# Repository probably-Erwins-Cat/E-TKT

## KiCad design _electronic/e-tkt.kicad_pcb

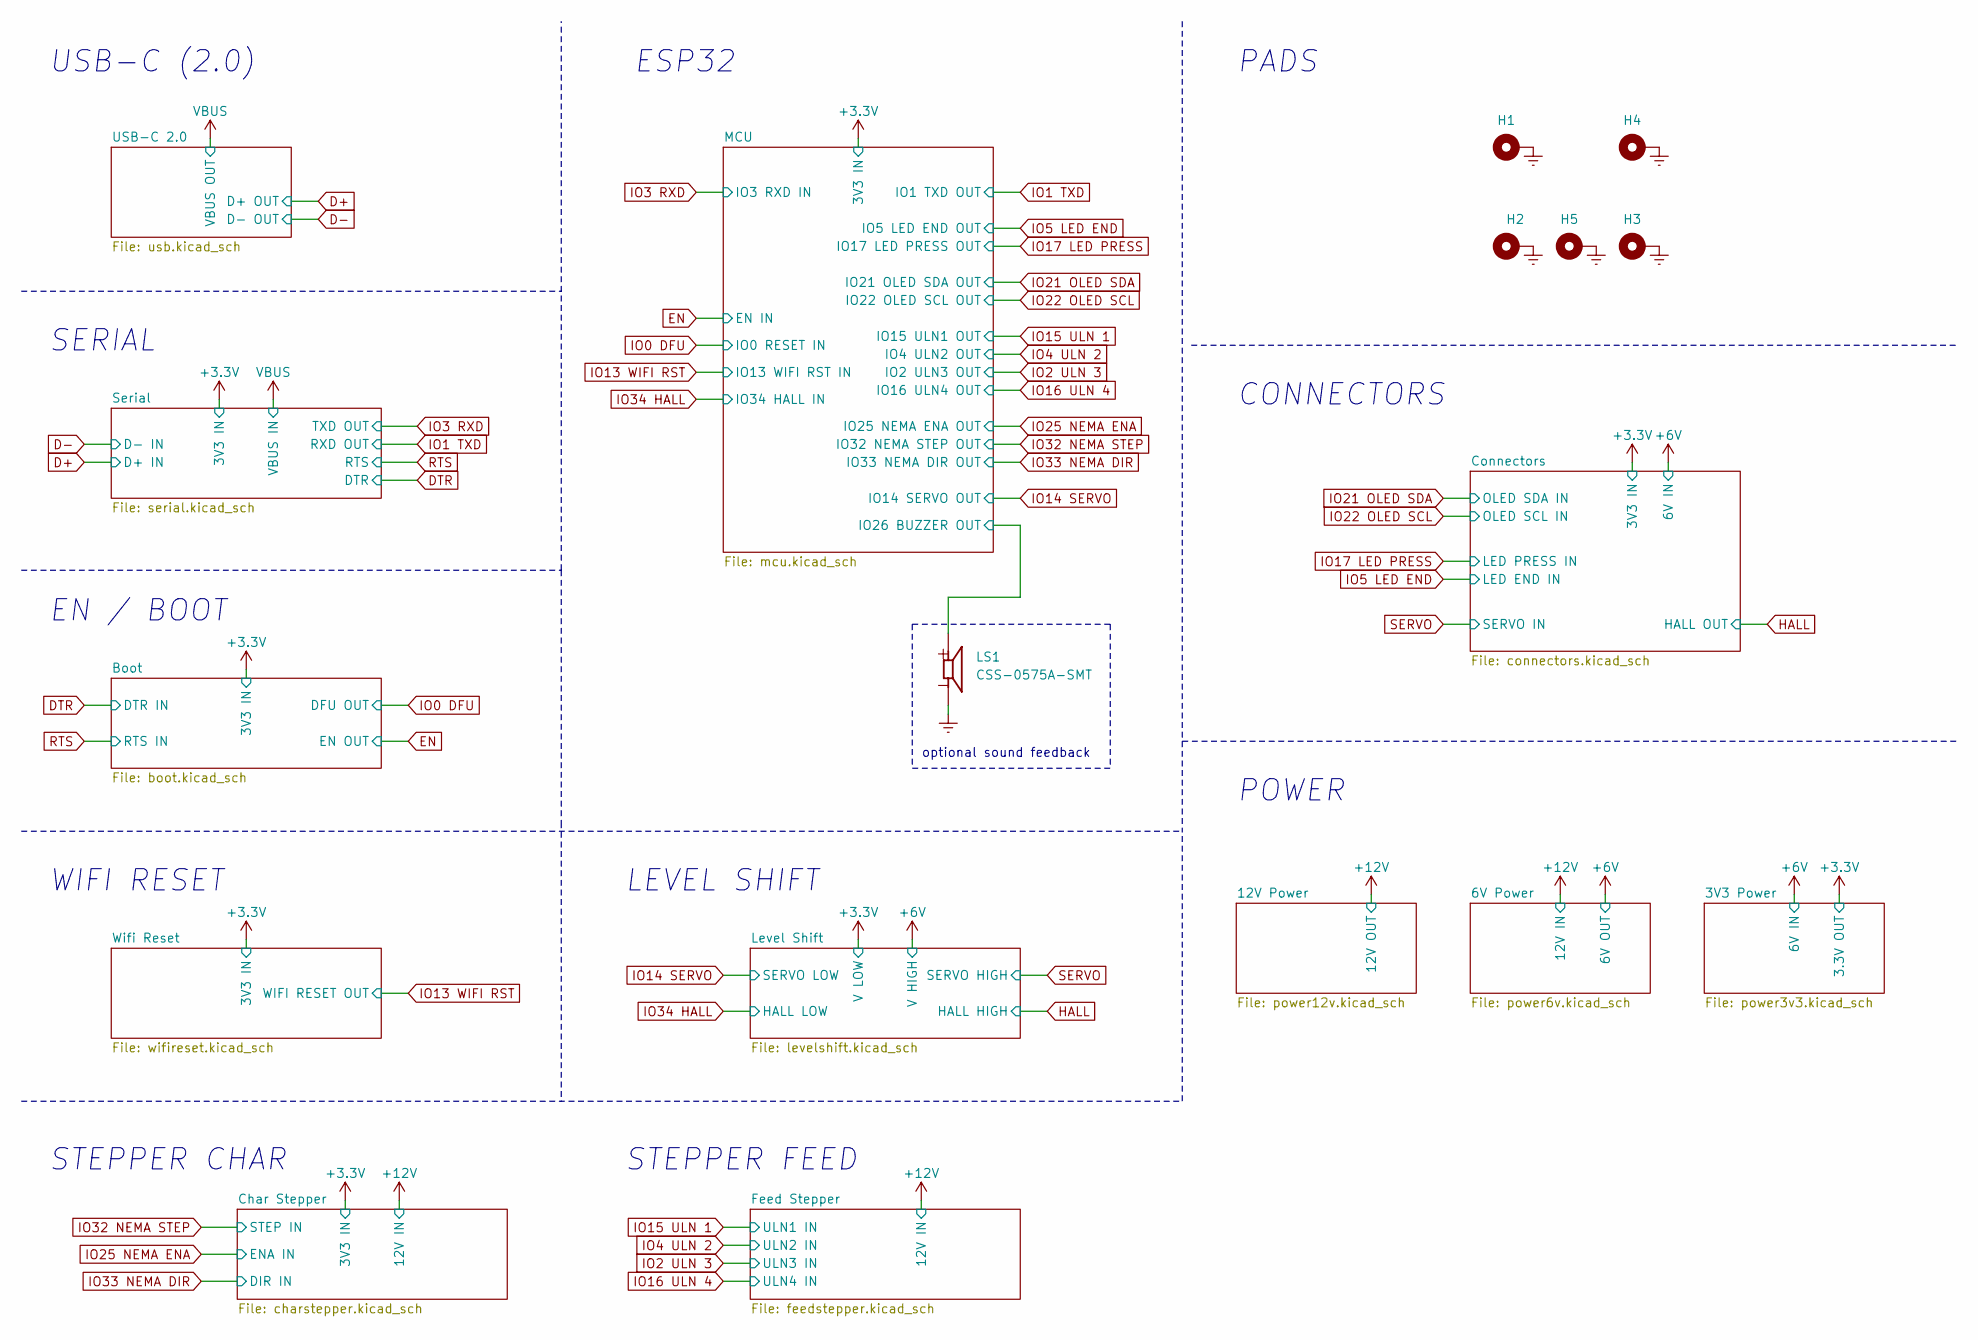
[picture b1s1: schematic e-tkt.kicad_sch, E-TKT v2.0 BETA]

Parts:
H1, H2, H3, H4, H5: M3; MountingHole_3.2mm_M3_Pad_Via; Mouser OK
LS1: CSS-0575A-SMT; BUZ-SMD_L5.0-W5.5-P4.60; Mouser OK

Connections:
/MCU/IO26 BUZZER OUT: LS1.1; also elsewhere on the board
GNDREF: H1.1, H2.1, H3.1, H4.1, H5.1, LS1.2; also elsewhere on the board

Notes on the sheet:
PADS
POWER
optional sound feedback
SERIAL
EN / BOOT
CONNECTORS
STEPPER CHAR
WIFI RESET
ESP32
LEVEL SHIFT
STEPPER FEED
USB-C (2.0)

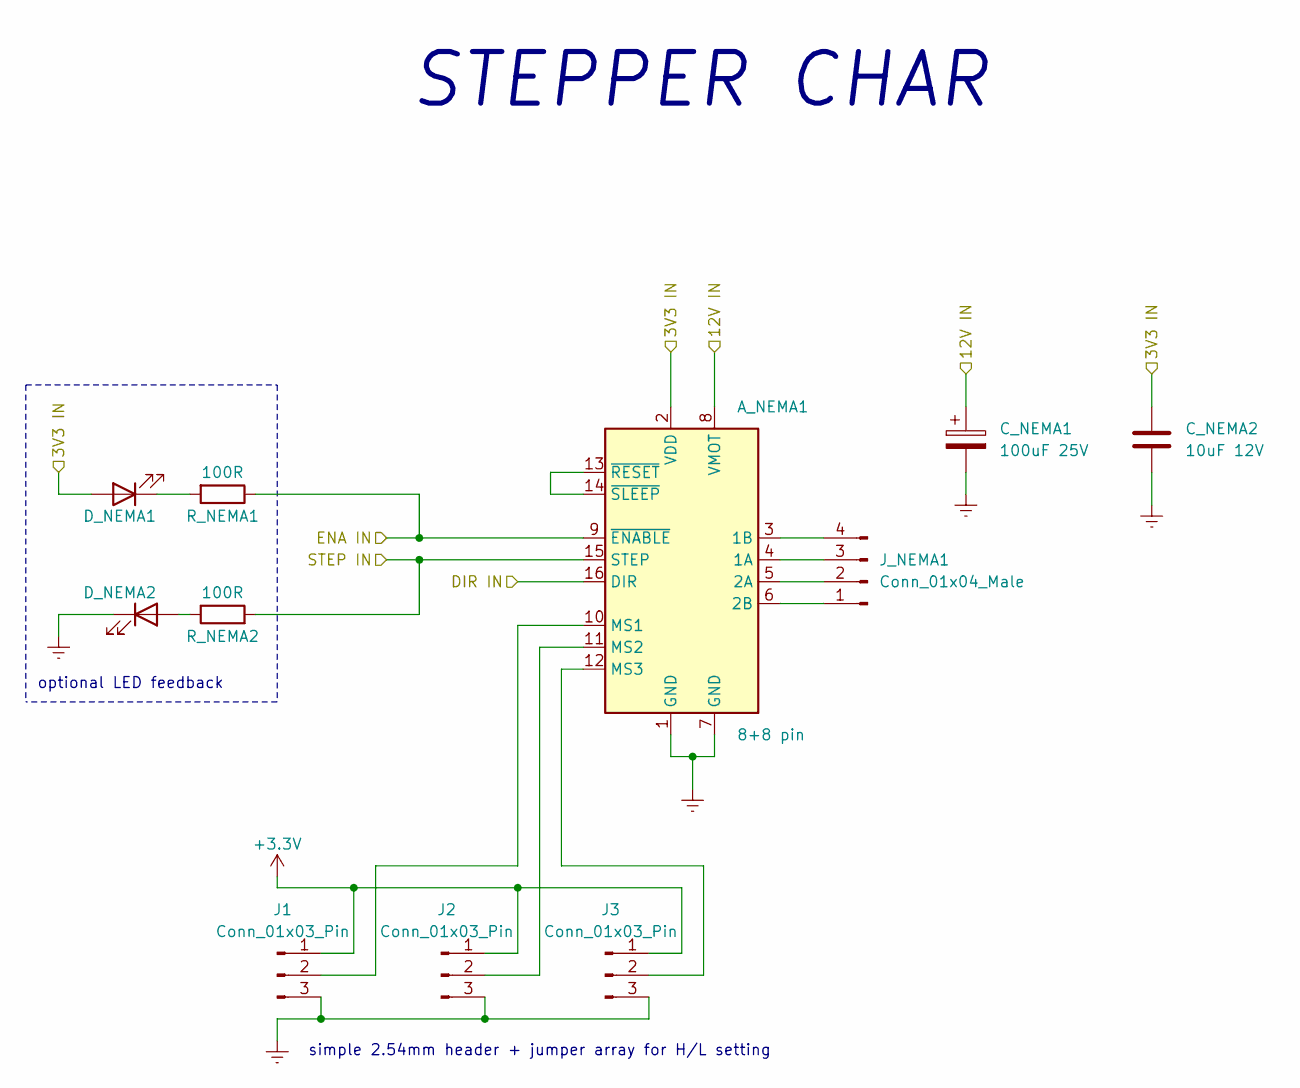
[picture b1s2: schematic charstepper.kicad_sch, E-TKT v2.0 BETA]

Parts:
A_NEMA1: 8+8 pin; Pololu_Breakout-16_15.2x20.3mm; Mouser OK
C_NEMA1: 100uF 25V; CP_Elec_6.3x7.7; Mouser OK
C_NEMA2: 10uF 12V; C_0603_1608Metric_Pad1.08x0.95mm_HandSolder; Mouser OK
D_NEMA1, D_NEMA2: LED white; LED_0603_1608Metric_Pad1.05x0.95mm_HandSolder; Mouser OK
J1, J2, J3: Conn_01x03_Pin; PinHeader_1x03_P2.54mm_Vertical; LCSC C2937625
J_NEMA1: Conn_01x04_Male; PinHeader_1x04_P2.54mm_Vertical; Mouser OK
R_NEMA1, R_NEMA2: 100R; R_0603_1608Metric_Pad0.98x0.95mm_HandSolder; Mouser OK

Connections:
+3.3V: A_NEMA1.2 (VDD), C_NEMA2.2, D_NEMA1.2 (A), J1.1, J2.1, J3.1; also elsewhere on the board
+12V: A_NEMA1.8 (VMOT), C_NEMA1.1; also elsewhere on the board
GNDREF: A_NEMA1.1 (GND), A_NEMA1.7 (GND), C_NEMA1.2, C_NEMA2.1, D_NEMA2.1 (K), J1.3, J2.3, J3.3; also elsewhere on the board
IO25 NEMA ENA: A_NEMA1.9 (~ENABLE), R_NEMA1.1; also elsewhere on the board
IO32 NEMA STEP: A_NEMA1.15 (STEP), R_NEMA2.2; also elsewhere on the board
IO33 NEMA DIR: A_NEMA1.16 (DIR); also elsewhere on the board
unnamed: A_NEMA1.4 (1A), J_NEMA1.3
unnamed: A_NEMA1.3 (1B), J_NEMA1.4
unnamed: A_NEMA1.5 (2A), J_NEMA1.2
unnamed: A_NEMA1.6 (2B), J_NEMA1.1
unnamed: A_NEMA1.10 (MS1), J1.2
unnamed: A_NEMA1.11 (MS2), J2.2
unnamed: A_NEMA1.12 (MS3), J3.2
unnamed: A_NEMA1.13 (~RESET), A_NEMA1.14 (~SLEEP)
unnamed: D_NEMA1.1 (K), R_NEMA1.2
unnamed: D_NEMA2.2 (A), R_NEMA2.1

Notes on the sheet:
optional LED feedback
simple 2.54mm header + jumper array for H/L setting
STEPPER CHAR

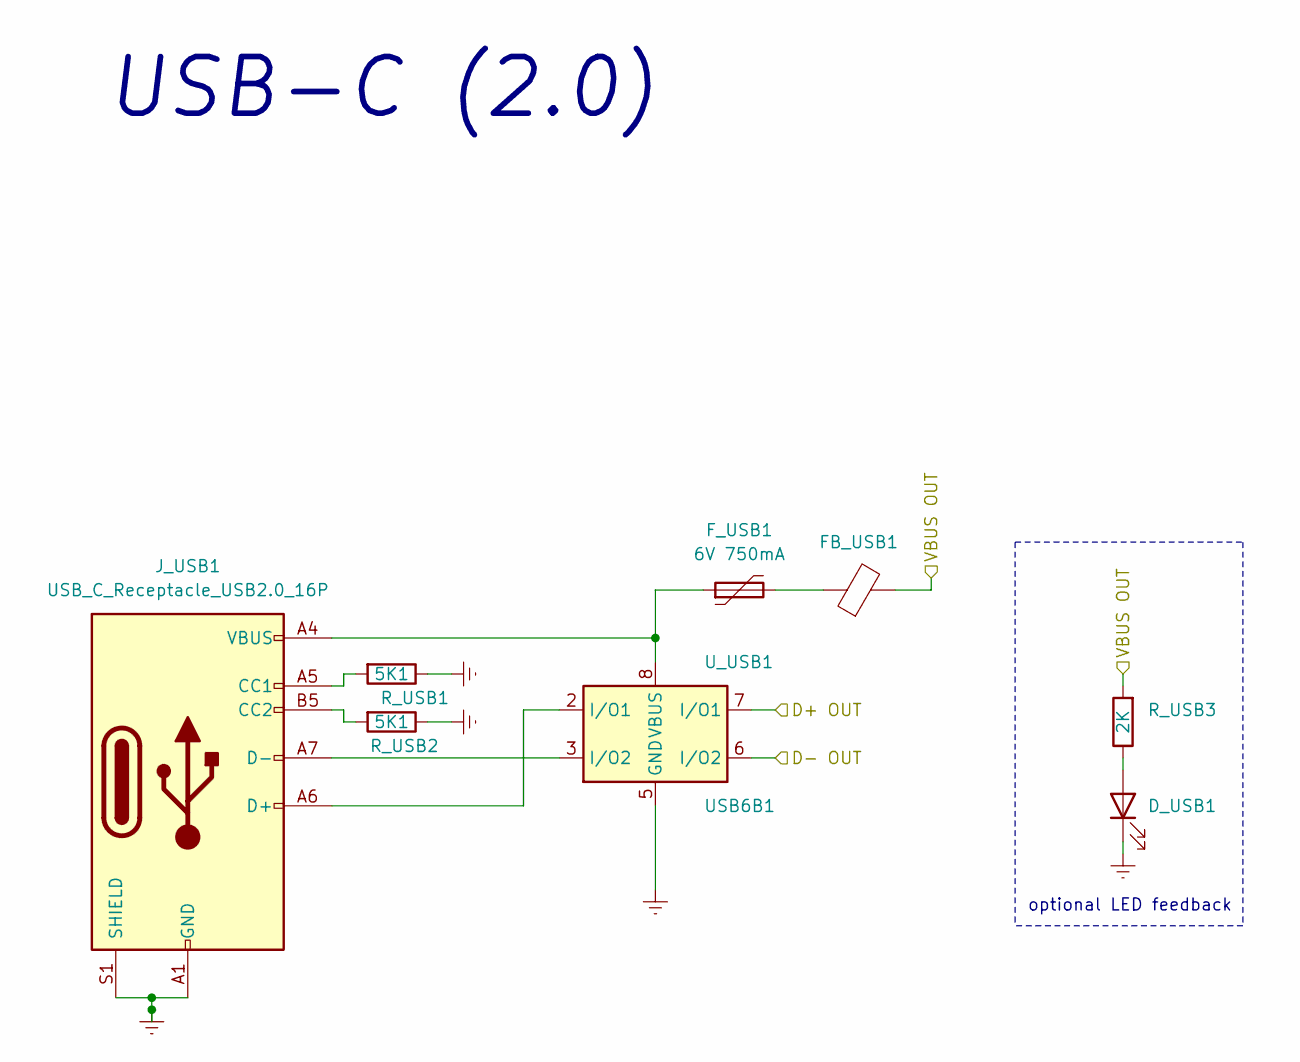
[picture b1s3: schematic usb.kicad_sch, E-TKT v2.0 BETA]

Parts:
D_USB1: LED white; LED_0603_1608Metric_Pad1.05x0.95mm_HandSolder; Mouser OK
FB_USB1: 40 Ohms @ 100 MHz 1 Power; L_0805_2012Metric_Pad1.05x1.20mm_HandSolder; Mouser OK
F_USB1: 6V 750mA; Fuse_0805_2012Metric_Pad1.15x1.40mm_HandSolder; Mouser OK
J_USB1: USB_C_Receptacle_USB2.0_16P; USB-TH_GT-USB-7057A; LCSC C22383830
R_USB1, R_USB2: 5K1; R_0603_1608Metric_Pad0.98x0.95mm_HandSolder; Mouser OK
R_USB3: 2K; R_0603_1608Metric_Pad0.98x0.95mm_HandSolder; Mouser OK
U_USB1: USB6B1; SOIC-8_3.9x4.9mm_P1.27mm; Mouser OK

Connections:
D+: U_USB1.7 (I/O1); also elsewhere on the board
D-: U_USB1.6 (I/O2); also elsewhere on the board
GNDREF: D_USB1.1 (K), J_USB1.A1 (GND), J_USB1.S1 (SHIELD), R_USB1.1, R_USB2.1, U_USB1.4 (GND), U_USB1.5 (GND); also elsewhere on the board
unnamed: D_USB1.2 (A), R_USB3.1
unnamed: FB_USB1.1, F_USB1.2
unnamed: F_USB1.1, J_USB1.A4 (VBUS), U_USB1.1 (VBUS), U_USB1.8 (VBUS)
unnamed: J_USB1.A5 (CC1), R_USB1.2
unnamed: J_USB1.B5 (CC2), R_USB2.2
unnamed: J_USB1.A6 (D+), U_USB1.2 (I/O1)
unnamed: J_USB1.A7 (D-), U_USB1.3 (I/O2)
VBUS: FB_USB1.2, R_USB3.2; also elsewhere on the board

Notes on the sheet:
USB-C (2.0)
optional LED feedback

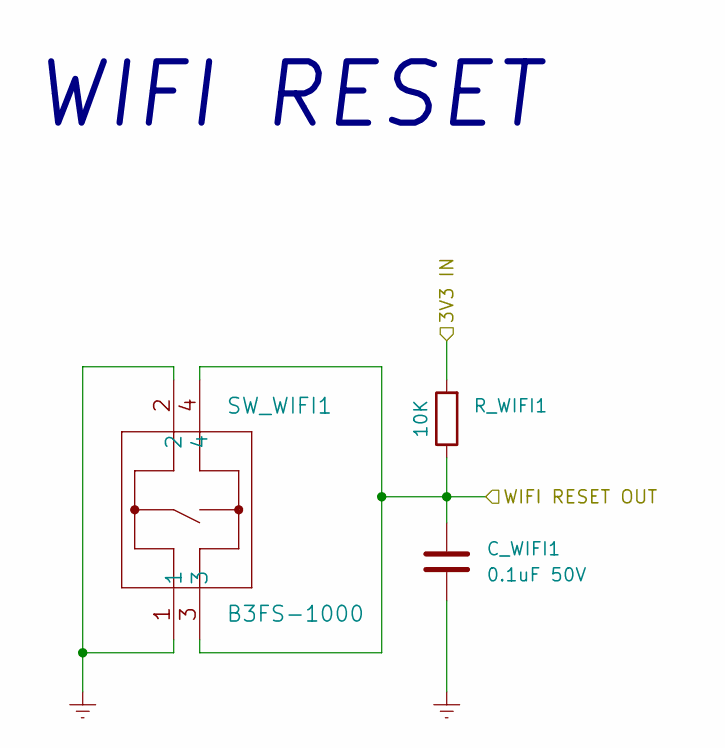
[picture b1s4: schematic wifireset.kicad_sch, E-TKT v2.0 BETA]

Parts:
C_WIFI1: 0.1uF 50V; C_0603_1608Metric_Pad1.08x0.95mm_HandSolder; Mouser OK
R_WIFI1: 10K; R_0603_1608Metric_Pad0.98x0.95mm_HandSolder; Mouser OK
SW_WIFI1: B3FS-1000; KEY-SMD_4P-L6.0-W6.3-P4.50-LS8.0; Mouser OK

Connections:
+3.3V: R_WIFI1.2; also elsewhere on the board
GNDREF: C_WIFI1.1, SW_WIFI1.1, SW_WIFI1.2; also elsewhere on the board
IO13 WIFI RST: C_WIFI1.2, R_WIFI1.1, SW_WIFI1.3, SW_WIFI1.4; also elsewhere on the board

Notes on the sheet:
WIFI RESET

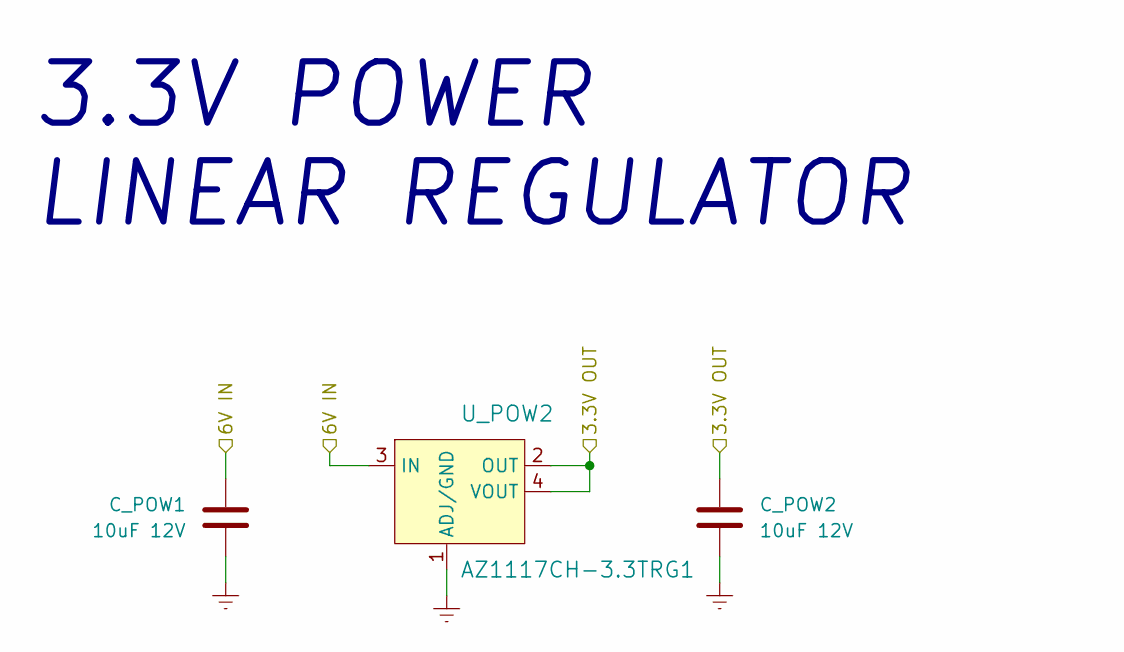
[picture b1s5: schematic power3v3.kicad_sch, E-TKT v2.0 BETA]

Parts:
C_POW1, C_POW2: 10uF 12V; C_0603_1608Metric_Pad1.08x0.95mm_HandSolder; Mouser OK
U_POW2: AZ1117CH-3.3TRG1; SOT-223; Mouser OK

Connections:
+3.3V: C_POW2.1, U_POW2.2 (OUT), U_POW2.4 (VOUT); also elsewhere on the board
+6V: C_POW1.1, U_POW2.3 (IN); also elsewhere on the board
GNDREF: C_POW1.2, C_POW2.2, U_POW2.1 (ADJ/GND); also elsewhere on the board

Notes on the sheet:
3.3V POWER LINEAR REGULATOR

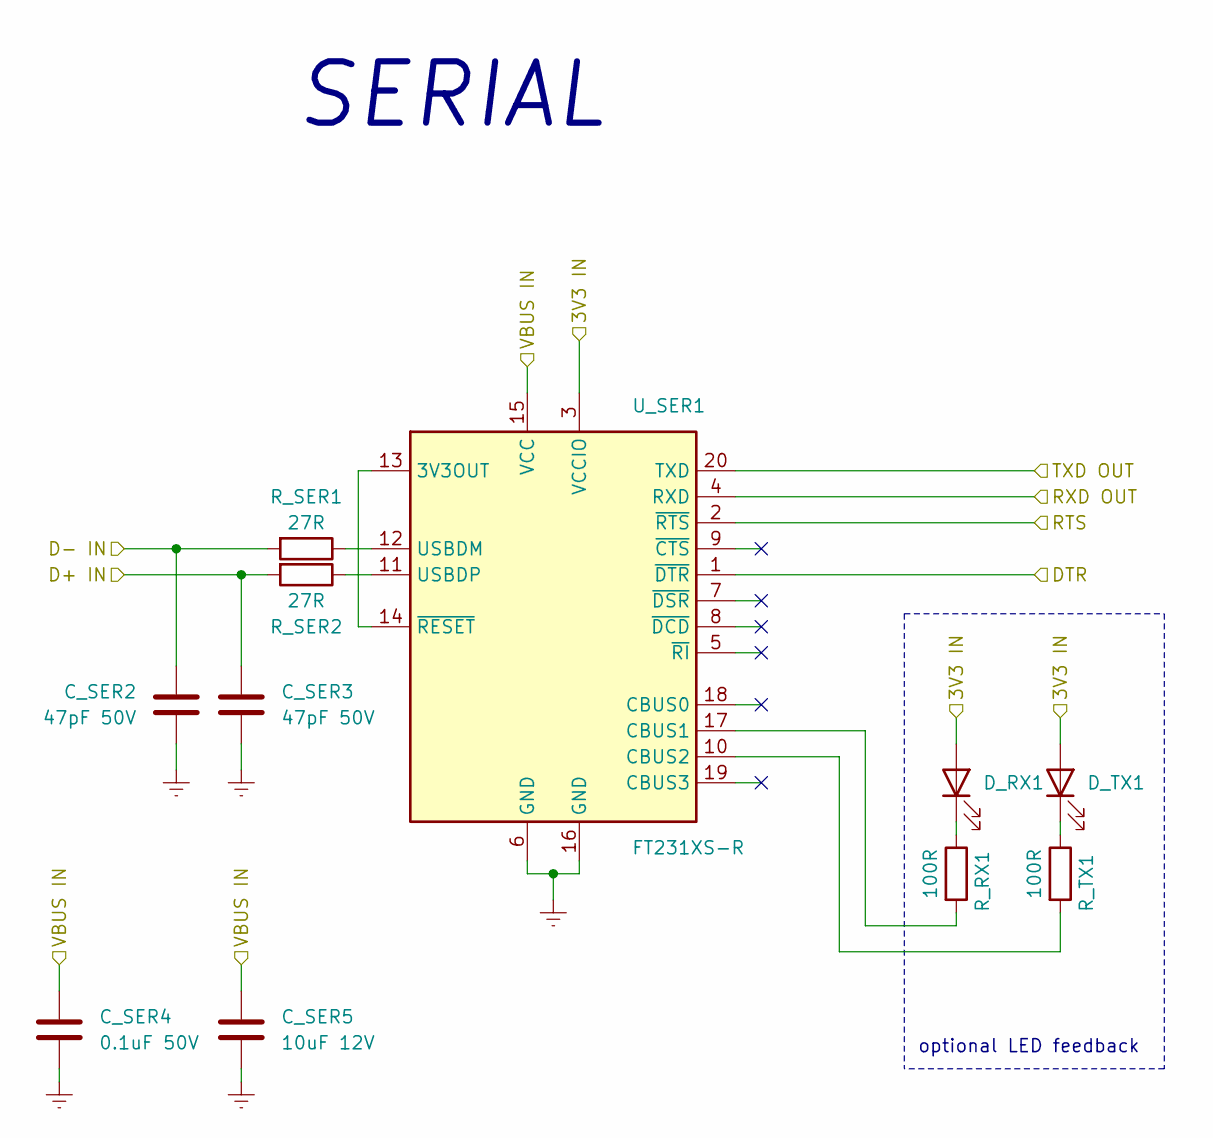
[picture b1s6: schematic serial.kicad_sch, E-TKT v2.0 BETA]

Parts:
C_SER2, C_SER3: 47pF 50V; C_0603_1608Metric_Pad1.08x0.95mm_HandSolder; Mouser OK
C_SER4: 0.1uF 50V; C_0603_1608Metric_Pad1.08x0.95mm_HandSolder; Mouser OK
C_SER5: 10uF 12V; C_0603_1608Metric_Pad1.08x0.95mm_HandSolder; Mouser OK
D_RX1: LED white; LED_0603_1608Metric_Pad1.05x0.95mm_HandSolder; Mouser OK
D_TX1: LED white; LED_0603_1608Metric_Pad1.05x0.95mm_HandSolder; Mouser OK
R_RX1: 100R; R_0603_1608Metric_Pad0.98x0.95mm_HandSolder; Mouser OK
R_SER1, R_SER2: 27R; R_0603_1608Metric_Pad0.98x0.95mm_HandSolder; Mouser OK
R_TX1: 100R; R_0603_1608Metric_Pad0.98x0.95mm_HandSolder; Mouser OK
U_SER1: FT231XS-R; SSOP-20_3.9x8.7mm_P0.635mm; Mouser OK

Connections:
+3.3V: D_RX1.2 (A), D_TX1.2 (A), U_SER1.3 (VCCIO); also elsewhere on the board
D+: C_SER3.2, R_SER2.2; also elsewhere on the board
D-: C_SER2.2, R_SER1.2; also elsewhere on the board
DTR: U_SER1.1 (~DTR); also elsewhere on the board
GNDREF: C_SER2.1, C_SER3.1, C_SER4.2, C_SER5.1, U_SER1.6 (GND), U_SER1.16 (GND); also elsewhere on the board
IO1 TXD: U_SER1.4 (RXD); also elsewhere on the board
IO3 RXD: U_SER1.20 (TXD); also elsewhere on the board
unnamed: D_RX1.1 (K), R_RX1.1
unnamed: D_TX1.1 (K), R_TX1.1
unnamed: U_SER1.13 (3V3OUT), U_SER1.14 (~RESET)
unnamed: R_RX1.2, U_SER1.17 (CBUS1)
unnamed: R_TX1.2, U_SER1.10 (CBUS2)
unnamed: R_SER1.1, U_SER1.12 (USBDM)
unnamed: R_SER2.1, U_SER1.11 (USBDP)
RTS: U_SER1.2 (~RTS); also elsewhere on the board
VBUS: C_SER4.1, C_SER5.2, U_SER1.15 (VCC); also elsewhere on the board

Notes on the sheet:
SERIAL
optional LED feedback

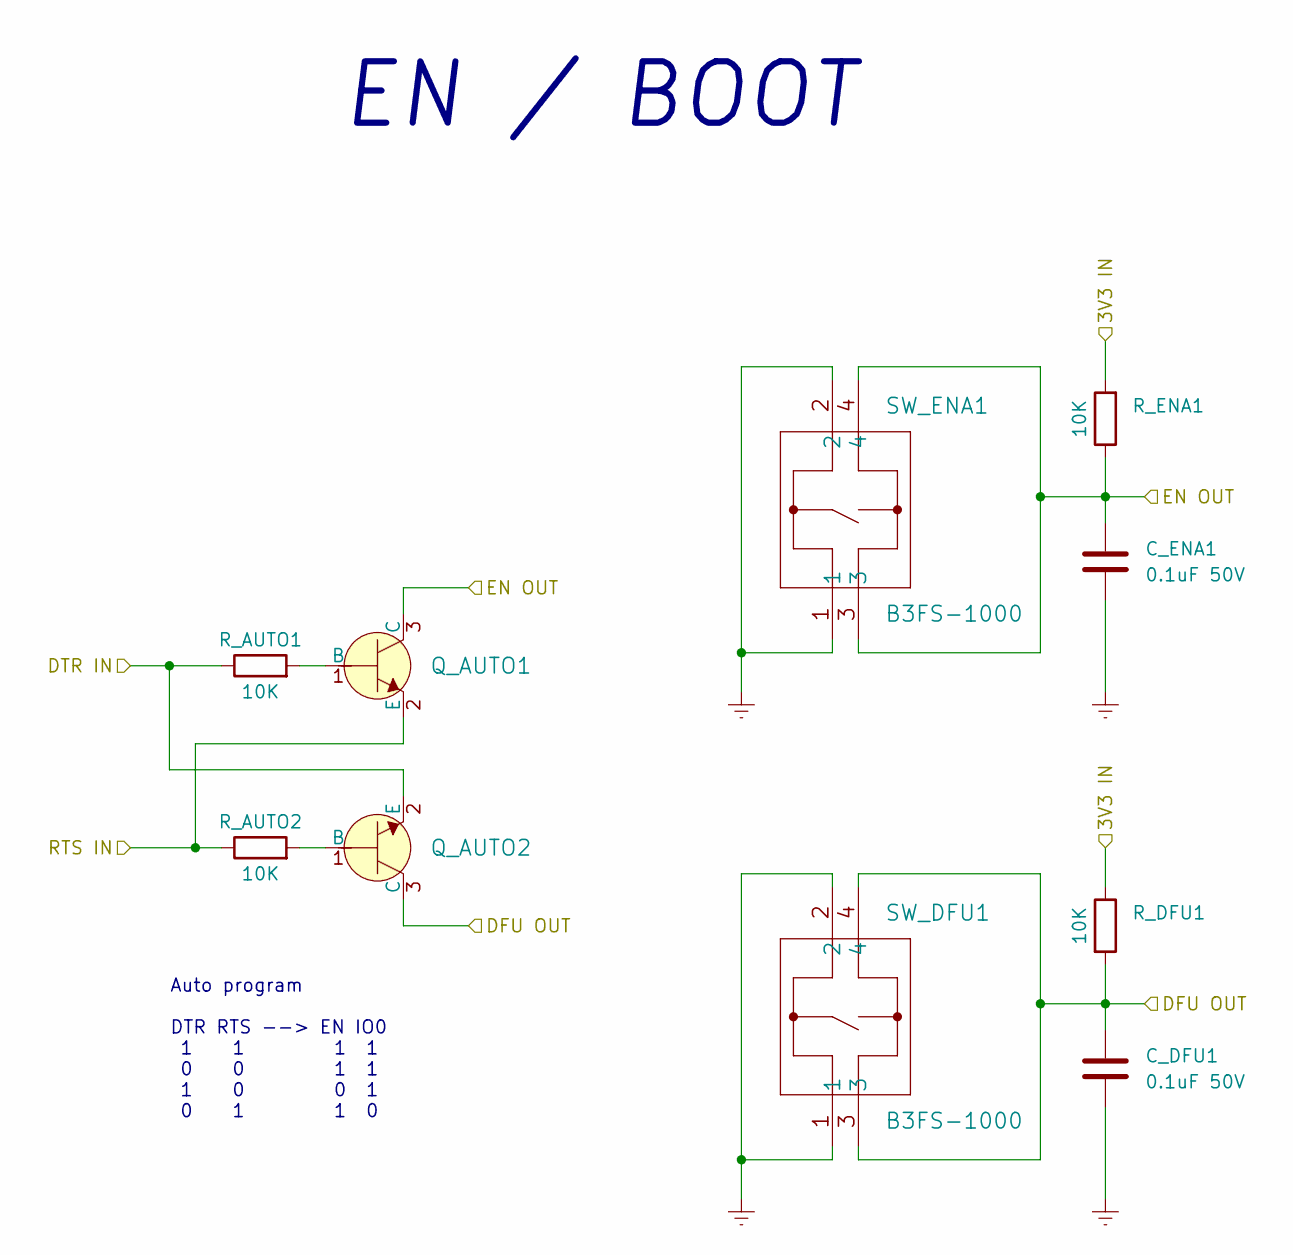
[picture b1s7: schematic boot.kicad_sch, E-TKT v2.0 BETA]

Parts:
C_DFU1: 0.1uF 50V; C_0603_1608Metric_Pad1.08x0.95mm_HandSolder; Mouser OK
C_ENA1: 0.1uF 50V; C_0603_1608Metric_Pad1.08x0.95mm_HandSolder; Mouser OK
Q_AUTO1, Q_AUTO2: SS8050; SOT-23_Handsoldering; Mouser OK
R_AUTO1, R_AUTO2: 10K; R_0603_1608Metric_Pad0.98x0.95mm_HandSolder; Mouser OK
R_DFU1: 10K; R_0603_1608Metric_Pad0.98x0.95mm_HandSolder; Mouser OK
R_ENA1: 10K; R_0603_1608Metric_Pad0.98x0.95mm_HandSolder; Mouser OK
SW_DFU1: B3FS-1000; KEY-SMD_4P-L6.0-W6.3-P4.50-LS8.0; Mouser OK
SW_ENA1: B3FS-1000; KEY-SMD_4P-L6.0-W6.3-P4.50-LS8.0; Mouser OK

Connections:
+3.3V: R_DFU1.1, R_ENA1.2; also elsewhere on the board
DTR: Q_AUTO2.2 (E), R_AUTO1.1; also elsewhere on the board
EN: C_ENA1.2, Q_AUTO1.3 (C), R_ENA1.1, SW_ENA1.3, SW_ENA1.4; also elsewhere on the board
GNDREF: C_DFU1.1, C_ENA1.1, SW_DFU1.1, SW_DFU1.2, SW_ENA1.1, SW_ENA1.2; also elsewhere on the board
IO0 DFU: C_DFU1.2, Q_AUTO2.3 (C), R_DFU1.2, SW_DFU1.3, SW_DFU1.4; also elsewhere on the board
unnamed: Q_AUTO1.1 (B), R_AUTO1.2
unnamed: Q_AUTO2.1 (B), R_AUTO2.2
RTS: Q_AUTO1.2 (E), R_AUTO2.1; also elsewhere on the board

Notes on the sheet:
Auto program DTR RTS --> EN IO0 1 1 1 1 0 0 1 1 1 0 0 1 0 1 1 0
EN / BOOT

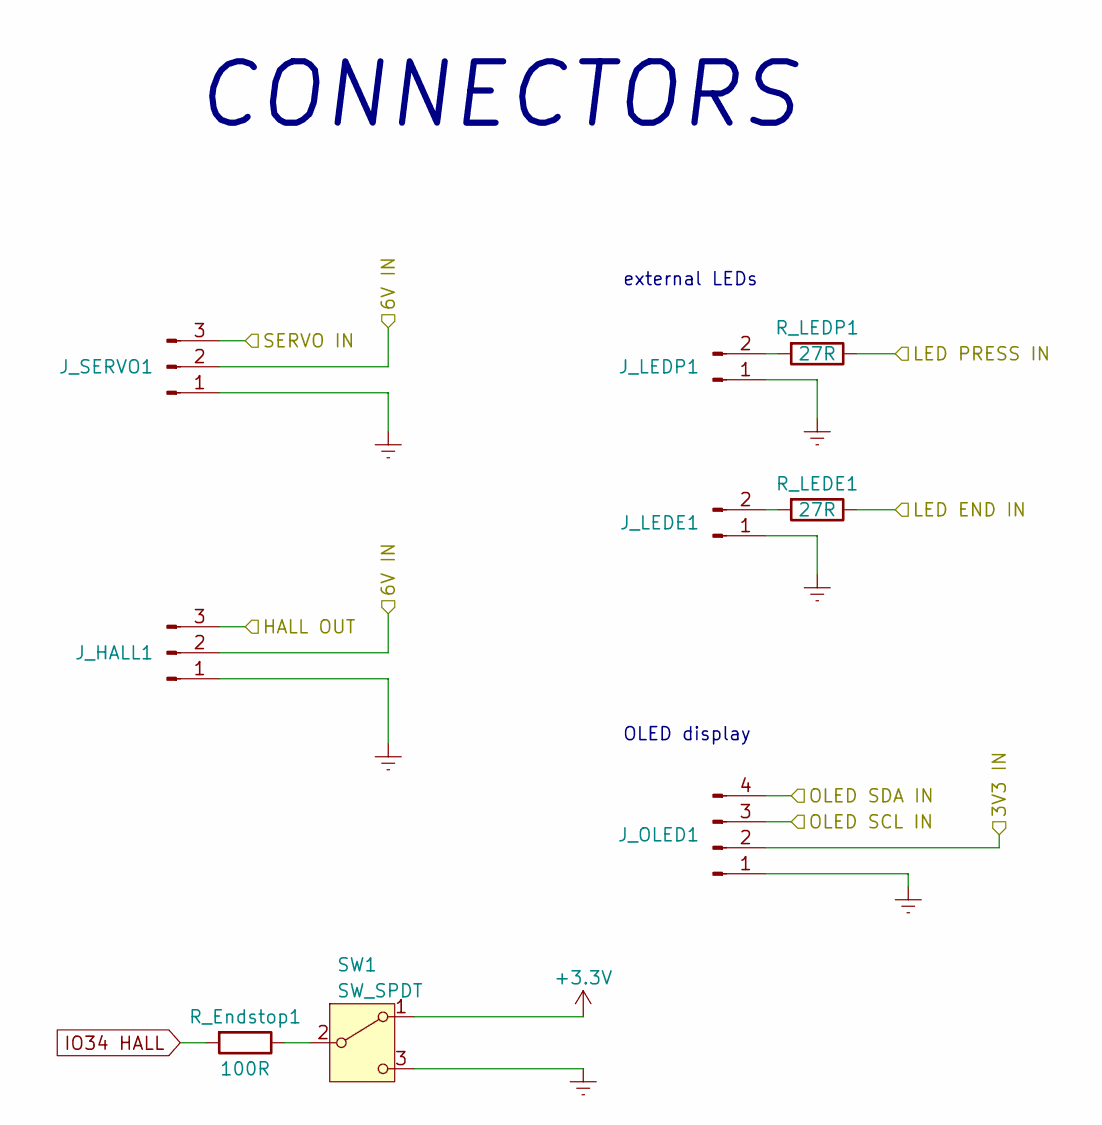
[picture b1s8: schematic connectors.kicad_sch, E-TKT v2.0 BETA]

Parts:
J_HALL1: Conn_01x03_Female; PinHeader_1x03_P2.54mm_Vertical; Mouser OK
J_LEDE1: Conn_01x02_Male; PinHeader_1x02_P2.54mm_Vertical; Mouser OK
J_LEDP1: Conn_01x02_Male; PinHeader_1x02_P2.54mm_Vertical; Mouser OK
J_OLED1: Conn_01x04_Male; PinHeader_1x04_P2.54mm_Vertical; Mouser OK
J_SERVO1: Conn_01x03_Male; PinHeader_1x03_P2.54mm_Vertical; Mouser OK
R_Endstop1: 100R; R_0603_1608Metric_Pad0.98x0.95mm_HandSolder; Mouser OK
R_LEDE1: 27R; R_0603_1608Metric_Pad0.98x0.95mm_HandSolder; Mouser OK
R_LEDP1: 27R; R_0603_1608Metric_Pad0.98x0.95mm_HandSolder; Mouser OK
SW1: SW_SPDT; SW-TH_JL010; LCSC C2681582

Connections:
+3.3V: J_OLED1.2, SW1.1 (A); also elsewhere on the board
+6V: J_HALL1.2, J_SERVO1.2; also elsewhere on the board
GNDREF: J_HALL1.1, J_LEDE1.1, J_LEDP1.1, J_OLED1.1, J_SERVO1.1, SW1.3 (C); also elsewhere on the board
HALL: J_HALL1.3; also elsewhere on the board
IO5 LED END: R_LEDE1.1; also elsewhere on the board
IO17 LED PRESS: R_LEDP1.1; also elsewhere on the board
IO21 OLED SDA: J_OLED1.4; also elsewhere on the board
IO22 OLED SCL: J_OLED1.3; also elsewhere on the board
IO34 HALL: R_Endstop1.2; also elsewhere on the board
unnamed: J_LEDE1.2, R_LEDE1.2
unnamed: J_LEDP1.2, R_LEDP1.2
unnamed: R_Endstop1.1, SW1.2 (B)
SERVO: J_SERVO1.3; also elsewhere on the board

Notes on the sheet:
OLED display
CONNECTORS
external LEDs

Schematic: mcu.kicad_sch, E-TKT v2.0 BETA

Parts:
C_MCU1: 0.1uF 50V; C_0603_1608Metric_Pad1.08x0.95mm_HandSolder; Mouser OK
C_MCU2: 10uF 12V; C_0603_1608Metric_Pad1.08x0.95mm_HandSolder; Mouser OK
U_MCU1: ESP32-WROOM-32; Mouser OK

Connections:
+3.3V: C_MCU1.1, C_MCU2.2, U_MCU1.2 (VDD); also elsewhere on the board
/MCU/IO26 BUZZER OUT: U_MCU1.11 (IO26); also elsewhere on the board
EN: U_MCU1.3 (EN); also elsewhere on the board
GNDREF: C_MCU1.2, C_MCU2.1, U_MCU1.1 (GND), U_MCU1.15 (GND), U_MCU1.38 (GND), U_MCU1.39 (GND); also elsewhere on the board
IO0 DFU: U_MCU1.25 (IO0); also elsewhere on the board
IO1 TXD: U_MCU1.35 (TXD0/IO1); also elsewhere on the board
IO2 ULN 3: U_MCU1.24 (IO2); also elsewhere on the board
IO3 RXD: U_MCU1.34 (RXD0/IO3); also elsewhere on the board
IO4 ULN 2: U_MCU1.26 (IO4); also elsewhere on the board
IO5 LED END: U_MCU1.29 (IO5); also elsewhere on the board
IO13 WIFI RST: U_MCU1.16 (IO13); also elsewhere on the board
IO14 SERVO: U_MCU1.13 (IO14); also elsewhere on the board
IO15 ULN 1: U_MCU1.23 (IO15); also elsewhere on the board
IO16 ULN 4: U_MCU1.27 (IO16); also elsewhere on the board
IO17 LED PRESS: U_MCU1.28 (IO17); also elsewhere on the board
IO21 OLED SDA: U_MCU1.33 (IO21); also elsewhere on the board
IO22 OLED SCL: U_MCU1.36 (IO22); also elsewhere on the board
IO25 NEMA ENA: U_MCU1.10 (IO25); also elsewhere on the board
IO32 NEMA STEP: U_MCU1.8 (IO32); also elsewhere on the board
IO33 NEMA DIR: U_MCU1.9 (IO33); also elsewhere on the board
IO34 HALL: U_MCU1.6 (IO34); also elsewhere on the board

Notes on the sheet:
ESP32

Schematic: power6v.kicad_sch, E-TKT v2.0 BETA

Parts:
C_POW_6V_FF1: 47pF 50V; C_0603_1608Metric_Pad1.08x0.95mm_HandSolder; Mouser OK
C_POW_BST1: 0.1uF 50V; C_0603_1608Metric_Pad1.08x0.95mm_HandSolder; Mouser OK
C_POW_IN1, C_POW_IN2, C_POW_IN3: 22uF 25V; C_1210_3225Metric_Pad1.33x2.70mm_HandSolder; Mouser OK
C_POW_OUT1, C_POW_OUT2, C_POW_OUT3, C_POW_OUT4, C_POW_OUT5: 22uF 25V; C_1210_3225Metric_Pad1.33x2.70mm_HandSolder; Mouser OK
L1: SRP6060FA-100M; IND-SMD_L8.5-W8.0_PSPMAA0803H-330M-ANP; Mouser OK
R_POW_FBT1: 100K; R_0603_1608Metric_Pad0.98x0.95mm_HandSolder; Mouser OK
R_POW_FFB1: 11K; R_0603_1608Metric_Pad0.98x0.95mm_HandSolder; Mouser OK
U_POW1: SOT-23-6_Handsoldering; Mouser N

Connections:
+6V: C_POW_6V_FF1.1, C_POW_OUT1.1, C_POW_OUT2.1, C_POW_OUT3.1, C_POW_OUT4.1, C_POW_OUT5.1, L1.2, R_POW_FBT1.2; also elsewhere on the board
+12V: C_POW_IN1.1, C_POW_IN2.1, C_POW_IN3.1, U_POW1.3 (VIN); also elsewhere on the board
GNDREF: C_POW_IN1.2, C_POW_IN2.2, C_POW_IN3.2, C_POW_OUT1.2, C_POW_OUT2.2, C_POW_OUT3.2, C_POW_OUT4.2, C_POW_OUT5.2, R_POW_FFB1.1, U_POW1.1 (GND); also elsewhere on the board
unnamed: C_POW_BST1.1, U_POW1.6 (BOOT)
unnamed: C_POW_6V_FF1.2, R_POW_FBT1.1, R_POW_FFB1.2, U_POW1.4 (FB)
unnamed: C_POW_BST1.2, L1.1, U_POW1.2 (SW)

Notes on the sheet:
6V POWER BUCK CONVERTER

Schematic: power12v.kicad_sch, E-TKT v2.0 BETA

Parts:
D_POW2: LED white; LED_0603_1608Metric_Pad1.05x0.95mm_HandSolder; Mouser OK
J_POW1: Barrel_Jack_Switch; BarrelJack_Horizontal; Mouser OK
J_USB2: USB_C_Receptacle_USB2.0_14P; USB-TH_GT-USB-7057A; LCSC C22383830
R_POW6: 5K1; R_0603_1608Metric_Pad0.98x0.95mm_HandSolder; Mouser OK
U1: HUSB237-AA001-DN06R; TDFN-6_L2.0-W2.0-P0.65-TL-EP; LCSC Part C22373734

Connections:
+12V: J_POW1.1, J_USB2.A4 (VBUS), R_POW6.1, U1.2 (VUSB); also elsewhere on the board
GNDREF: D_POW2.1 (K), J_POW1.2, J_POW1.3, J_USB2.A1 (GND), J_USB2.S1 (SHIELD), U1.7 (GND); also elsewhere on the board
unnamed: D_POW2.2 (A), R_POW6.2
unnamed: J_USB2.A5 (CC1), U1.1 (CC1)
unnamed: J_USB2.B5 (CC2), U1.6 (CC2)

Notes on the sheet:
Vset = floating =12V
optional LED feedback
12V POWER + LATCH SWITCH

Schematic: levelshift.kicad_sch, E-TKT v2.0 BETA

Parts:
D_HALL1: LED white; LED_0603_1608Metric_Pad1.05x0.95mm_HandSolder; Mouser OK
D_SERVO1: LED white; LED_0603_1608Metric_Pad1.05x0.95mm_HandSolder; Mouser OK
Q_HALL1: BSS138LT3G; SOT-23_Handsoldering; Mouser OK
Q_SERVO1: BSS138LT3G; SOT-23_Handsoldering; Mouser OK
R_HALL1, R_HALL2: 10K; R_0603_1608Metric_Pad0.98x0.95mm_HandSolder; Mouser OK
R_HALL3: 100R; R_0603_1608Metric_Pad0.98x0.95mm_HandSolder; Mouser OK
R_SERVO1, R_SERVO2: 10K; R_0603_1608Metric_Pad0.98x0.95mm_HandSolder; Mouser OK
R_SERVO3: 100R; R_0603_1608Metric_Pad0.98x0.95mm_HandSolder; Mouser OK

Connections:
+3.3V: D_HALL1.2 (A), D_SERVO1.2 (A), Q_HALL1.1 (G), Q_SERVO1.1 (G), R_HALL2.2, R_SERVO2.2; also elsewhere on the board
+6V: R_HALL1.2, R_SERVO1.2; also elsewhere on the board
HALL: Q_HALL1.3 (D), R_HALL1.1; also elsewhere on the board
IO14 SERVO: Q_SERVO1.2 (S), R_SERVO2.1, R_SERVO3.1; also elsewhere on the board
IO34 HALL: Q_HALL1.2 (S), R_HALL2.1, R_HALL3.1; also elsewhere on the board
unnamed: D_HALL1.1 (K), R_HALL3.2
unnamed: D_SERVO1.1 (K), R_SERVO3.2
SERVO: Q_SERVO1.3 (D), R_SERVO1.1; also elsewhere on the board

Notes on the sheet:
optional LED feedback
LEVEL SHIFT

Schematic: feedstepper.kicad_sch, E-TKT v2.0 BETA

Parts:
C_STP1: 10uF 12V; C_0603_1608Metric_Pad1.08x0.95mm_HandSolder; Mouser OK
D_STP1, D_STP2, D_STP3, D_STP4: LED white; LED_0603_1608Metric_Pad1.05x0.95mm_HandSolder; Mouser OK
J_28byj-48-12v_1: Conn_01x05_Male; PinHeader_1x05_P2.54mm_Vertical; Mouser OK
R_STP1, R_STP2, R_STP3, R_STP4: 5K1; R_0603_1608Metric_Pad0.98x0.95mm_HandSolder; Mouser OK
U_STP1: ULN2003; SOIC-16_3.9x9.9mm_P1.27mm; Mouser OK

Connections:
+12V: C_STP1.2, J_28byj-48-12v_1.1, R_STP1.1, R_STP2.1, R_STP3.1, R_STP4.1, U_STP1.9 (COM); also elsewhere on the board
GNDREF: C_STP1.1, U_STP1.8 (GND); also elsewhere on the board
IO2 ULN 3: U_STP1.3 (I3); also elsewhere on the board
IO4 ULN 2: U_STP1.2 (I2); also elsewhere on the board
IO15 ULN 1: U_STP1.1 (I1); also elsewhere on the board
IO16 ULN 4: U_STP1.4 (I4); also elsewhere on the board
unnamed: D_STP1.2 (A), R_STP1.2
unnamed: D_STP1.1 (K), J_28byj-48-12v_1.2, U_STP1.16 (O1)
unnamed: D_STP2.2 (A), R_STP2.2
unnamed: D_STP2.1 (K), J_28byj-48-12v_1.3, U_STP1.15 (O2)
unnamed: D_STP3.2 (A), R_STP3.2
unnamed: D_STP3.1 (K), J_28byj-48-12v_1.4, U_STP1.14 (O3)
unnamed: D_STP4.2 (A), R_STP4.2
unnamed: D_STP4.1 (K), J_28byj-48-12v_1.5, U_STP1.13 (O4)

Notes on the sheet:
optional LED feedback
STEPPER FEED

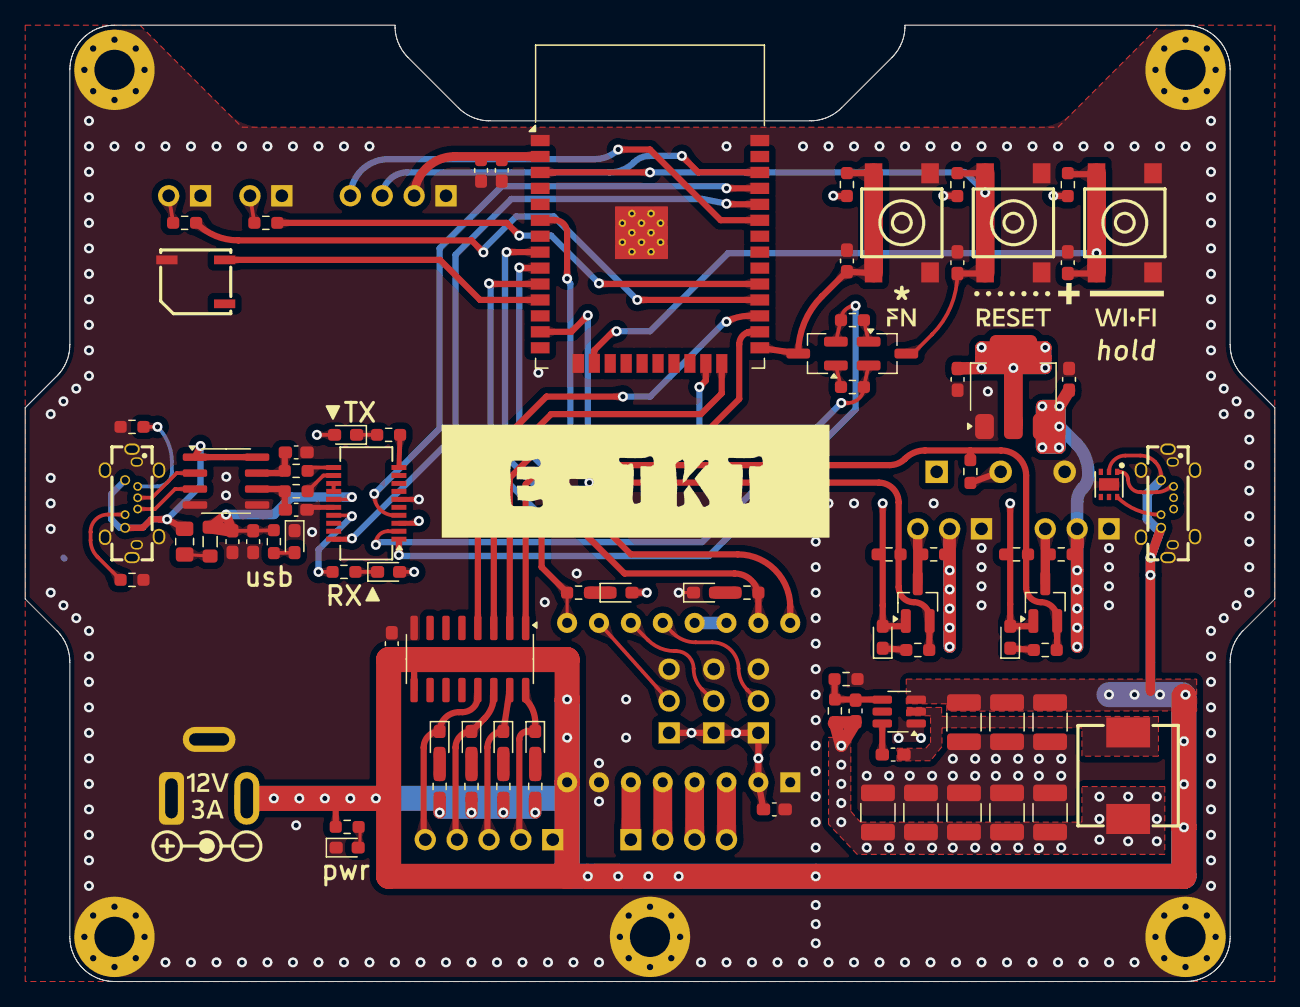
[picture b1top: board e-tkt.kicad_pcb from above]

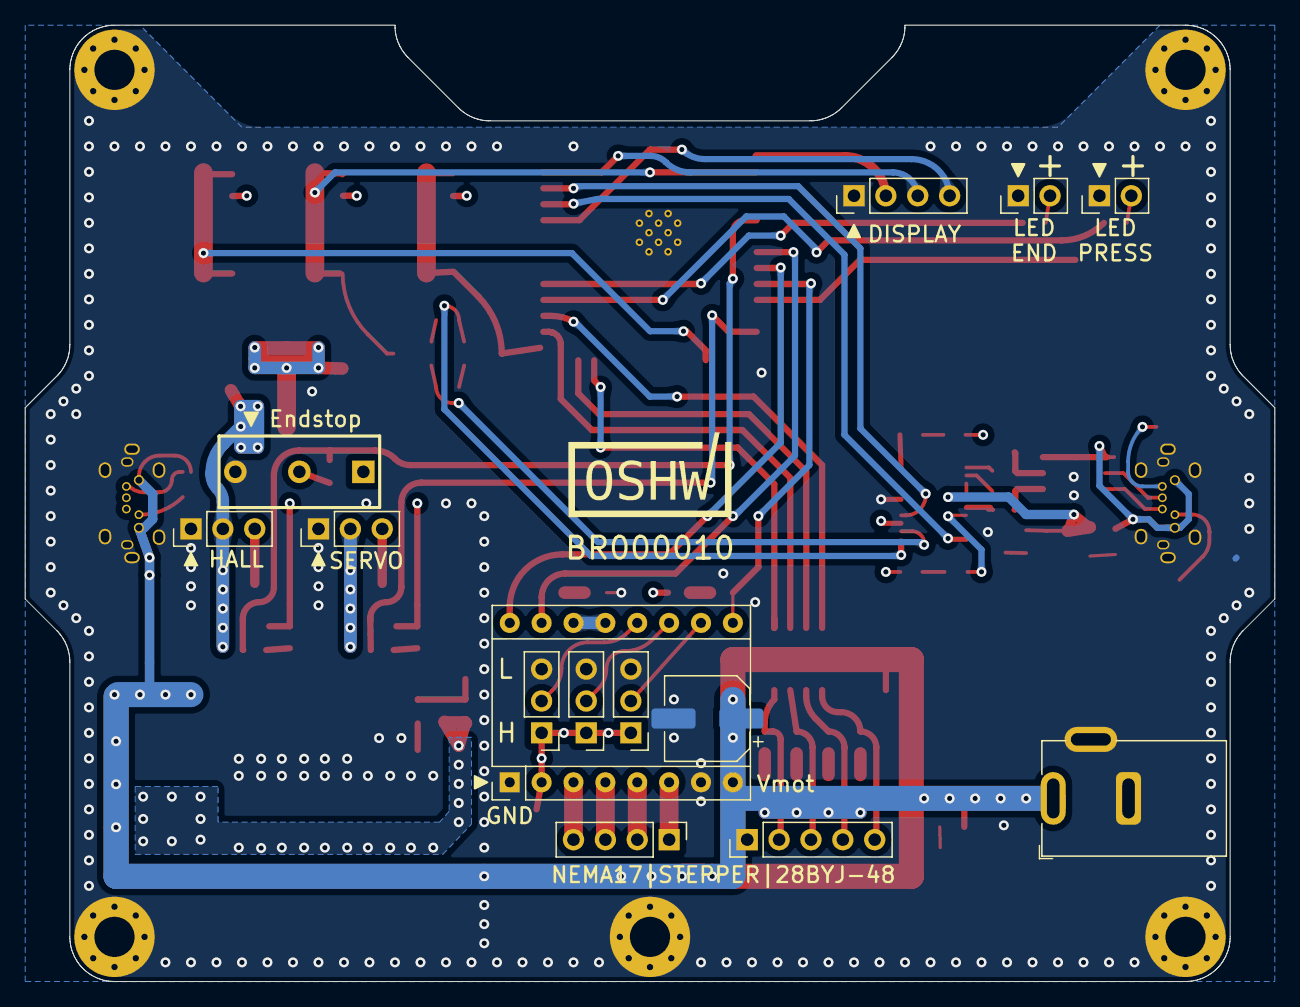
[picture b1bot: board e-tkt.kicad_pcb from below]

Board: 4 copper layers, 99.6 x 76.2 mm, 104 parts (14 on the bottom side), 75 nets.

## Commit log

2025-10-15 BETA first upload
    nothing major done here:
    * updated KiCAD files to v9
    * removed alternative 6v feed-in. The proposed buck converter is fine.
    * added to all components LCSC component IDs. With this, exporting the project as gerber files also automatically creates correct BOM for JLCPCB manufacturing
    *
2025-10-15 Added CAD, cleaned up KiCAD some more
    Added a FreeCAD Assembly. This will serve for minor updated to the printable parts.
    Updated USB-C component to standard KiCAD libary-integrated version, because the pinout of the schematic symbol was messing with the pinout of the footprint
    exported the PCB as step so it could be imported to FreeCAD
2025-10-16 Updated A_bottom in FreeCAD
    added pockets for M3 nuts, added pockets for electronics cover
    started to optimize pcb footprint layout and voltage reference planes
2025-10-16 Minor adjustments of CAD and EDA
2025-10-16 Updating KiCAD files
    some footprints in KicCAD v9 were updated versus v6 and threw warnings/errors. All footprints are now v9 compatible
    wiring from ESP32 pins was optimized
    layout of servo and hall level shift was optimized
    layer 3 was split in 6V plane around the DCDC and 3V3 plane around everywhere else
2025-10-20 Decluttering traces and Compactifying Part placement
    many parts have been place in a compact format,
    footprint layout optimized for function and visuals
2025-10-20 USB-C PD added
    in parallel to DC jack, realized via HUSB237
2025-10-21 Updated USB-C PD layout and zoning
2025-10-21 Optimized alignment of USB-C socket
    so that there is more tolerance for printed parts
2025-10-21 pillars F G optimized
    for optional electronics cover and added M3 nut slots
2025-10-21 added pillars with nut pocket
2025-10-22 Added endstop
    added footprint for a microswitch with roller as enstop. updated the CAD correspondingly by adding M4 hole in the nema wheel hub for an M4 12mm/16mm set screw (the ones with a pointy end).
2025-10-23 sturdyfy E-TKT
2025-10-23 Sturdify CAD
2025-10-23 sturdify again
2025-10-23 JLC export added, LCSC numbers updated
2025-10-24 Updated layout of schematic symbol's text
